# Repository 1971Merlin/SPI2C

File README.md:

# SPI2C
SPI2C interface hardware and software for the TEC-1 and SC-1 family of Z80 single board computers.

The full [construction article](SPI%20and%20I2C%20Article%20Final.pdf) PDF describes the SPI2C board in detail.

Please see https://github.com/tec1group for information on the TEC computer.

**spi2c_library.asm** contains the current code libraries for interfacing with the SPI2C board. Note the IO ports you choose to use will need to be edite in this file, if you're building for the TEC-1 hardware. The settings are correct for use with the SC-1 as provided.

PS2 Keyboard or Mouse contains sample code and circuit for hooking up a regular IBM PC compatible PS/2 or AT keyboard, or, a PS/2 mouse to the SPI2C.

-------------------------------------------------

The following code examples are early test releases and not all of them use the above library.

**spi_7segs.asm** links an 8 digit, 7-segment display (SPI bus, Duinotech XC-3714) to the SC1. 

**i2c test.asm** code expands on the first sample, adding a DS1307 based clock module (i2c bus, Duinotech XC-4450) which then displays the time on the 7-segment SPI board. The i2c code is also designed to be 'universal', compiling for either the TEC-1 or the SC-1 hardware platforms.

**i2c bus scan.asm** scans the entire i2c bus and displays the address of any detected i2c device on the 7-seg displays. press any key to display the next device. FFh displayed means 'no devices found'.

**5110.asm** displays an image on an SPI bus based 'Nokia 5510' or PCD8544 display, i.e. a standard 84x48 monochrome LCD.

**Game of Life 5110.asm** Game of Life is a cellular automation program developed in 1970. https://en.wikipedia.org/wiki/Conway%27s_Game_of_Life It is a popular routine to reproduce an many computing platforms, as the algorithm is quite simple and memory etc. requirements are also fairly minimal. In this version we use the SPI2C board and the Nokia 5110 LCD display as the output device. The program can be compiled with either a random or a fixed pattern starting point.

**maze 5100.asm** A simple maze program, made famous by the well known Commodore 64 basic code

````10 PRINT CHR$(205.5+RND(1)); : GOTO 10.````

Outputs to the 84x48 "Nokia 5110" LCD display.

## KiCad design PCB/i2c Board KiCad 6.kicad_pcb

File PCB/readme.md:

KiCad PCB Files for this project

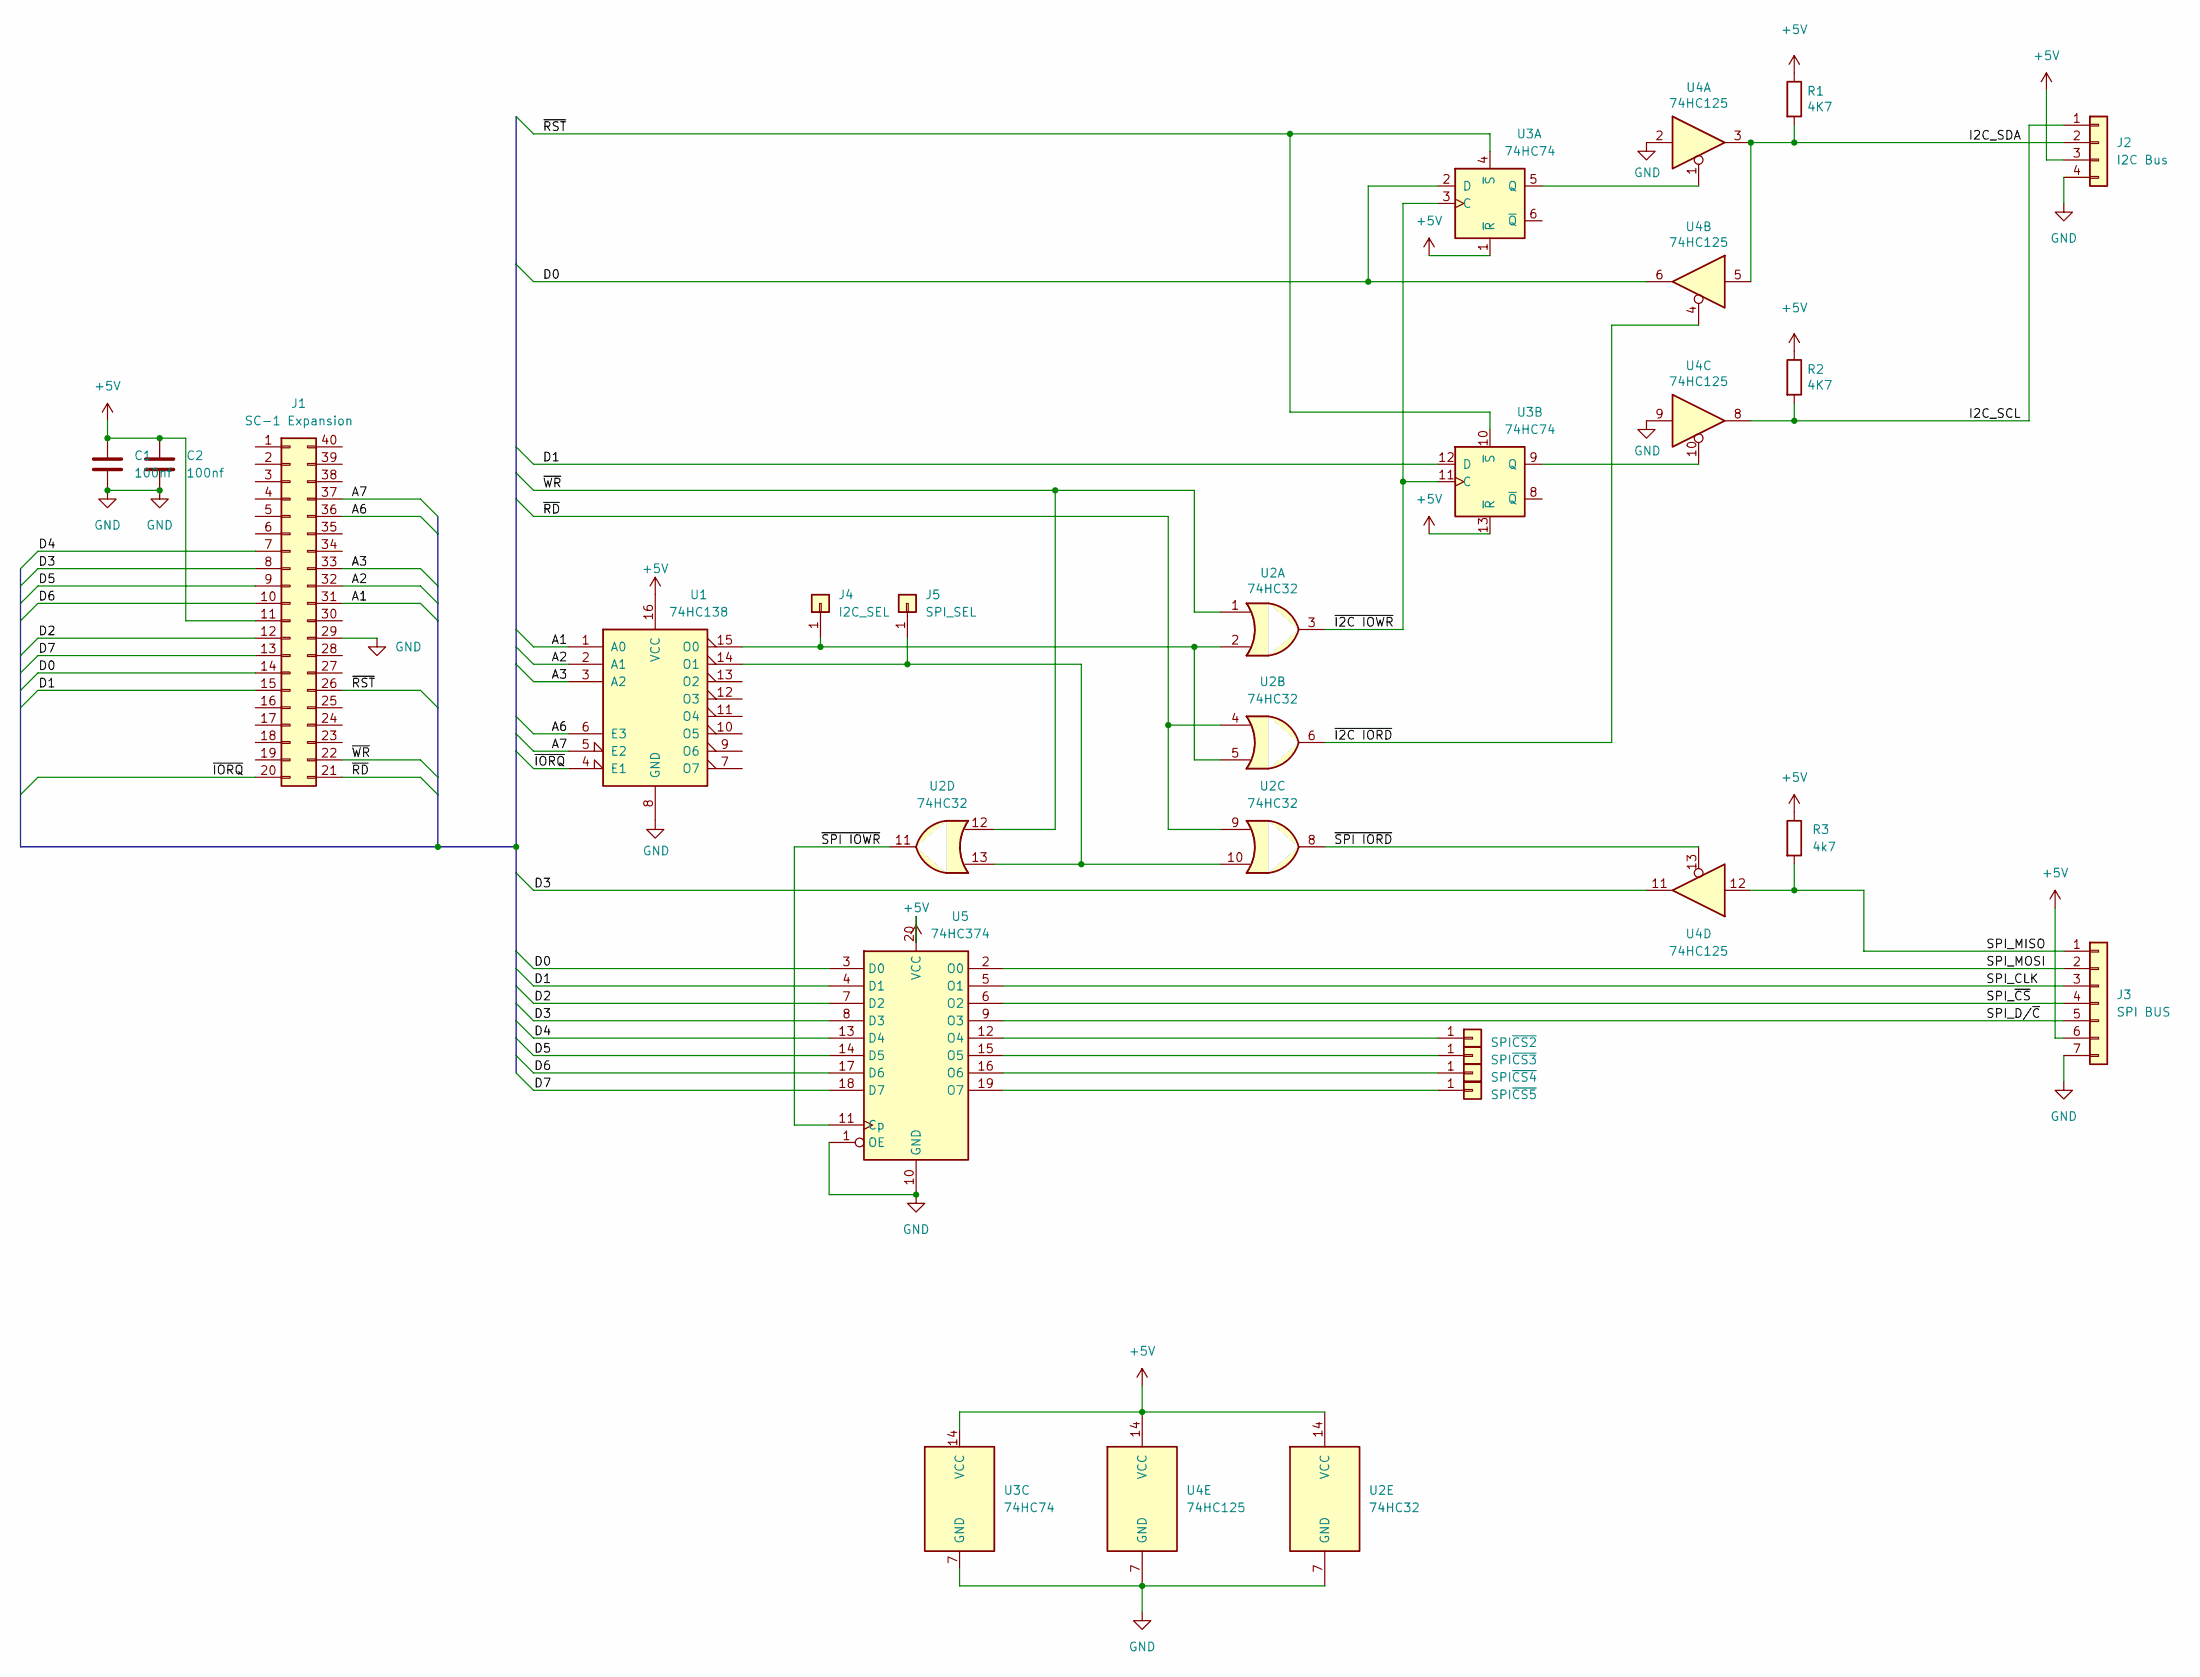
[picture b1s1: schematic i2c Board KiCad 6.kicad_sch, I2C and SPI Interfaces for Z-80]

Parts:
C1, C2: 100nf; C_Rect_L7.0mm_W2.0mm_P5.00mm
J1: SC-1 Expansion; SC-1 CPU IDC Header
J2: I2C Bus; PinSocket_1x04_P2.54mm_Vertical
J3: SPI BUS; PinSocket_1x07_P2.54mm_Vertical
J4: I2C_SEL; Pin_D1.0mm_L10.0mm
J5: SPI_SEL; Pin_D1.0mm_L10.0mm
J6: SPI~{CS2}; Pin_D1.0mm_L10.0mm
J7: SPI~{CS3}; Pin_D1.0mm_L10.0mm
J8: SPI~{CS4}; Pin_D1.0mm_L10.0mm
J9: SPI~{CS5}; Pin_D1.0mm_L10.0mm
R1, R2: 4K7; R_Axial_DIN0204_L3.6mm_D1.6mm_P5.08mm_Horizontal
R3: 4k7; R_Axial_DIN0204_L3.6mm_D1.6mm_P5.08mm_Horizontal
U1: 74HC138; DIP-16_W7.62mm_Socket
U2: 74HC32; DIP-14_W7.62mm_Socket
U3: 74HC74; DIP-14_W7.62mm_Socket
U4: 74HC125; DIP-14_W7.62mm_Socket
U5: 74HC374; DIP-20_W7.62mm_Socket

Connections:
+5V: C1.1, C2.1, J1.11, J2.3, J3.6, R1.1, R2.1, R3.1, U1.16 (VCC), U2.14 (VCC), U3.1 (~R), U3.13 (~R), U3.14 (VCC), U4.14 (VCC), U5.20 (VCC)
/A1: J1.31, U1.1 (A0)
/A2: J1.32, U1.2 (A1)
/A3: J1.33, U1.3 (A2)
/A6: J1.36, U1.6 (E3)
/A7: J1.37, U1.5 (E2)
/D0: J1.14, U3.2 (D), U4.6, U5.3 (D0)
/D1: J1.15, U3.12 (D), U5.4 (D1)
/D2: J1.12, U5.7 (D2)
/D3: J1.8, U4.11, U5.8 (D3)
/D4: J1.7, U5.13 (D4)
/D5: J1.9, U5.14 (D5)
/D6: J1.10, U5.17 (D6)
/D7: J1.13, U5.18 (D7)
/I2C_SCL: J2.1, R2.2, U4.8
/I2C_SDA: J2.2, R1.2, U4.3, U4.5
/SPI_CLK: J3.3, U5.5 (O1)
/SPI_D/~C: J3.5, U5.9 (O3)
/SPI_MISO: J3.1, R3.2, U4.12
/SPI_MOSI: J3.2, U5.2 (O0)
/SPI_~CS: J3.4, U5.6 (O2)
/~I2C IORD: U2.6, U4.4
/~I2C IOWR: U2.3, U3.3 (C), U3.11 (C)
/~IORQ: J1.20, U1.4 (E1)
/~RD: J1.21, U2.4, U2.9
/~RST: J1.26, U3.4 (~S), U3.10 (~S)
/~SPI IORD: U2.8, U4.13
/~SPI IOWR: U2.11, U5.11 (Cp)
/~WR: J1.22, U2.1, U2.12
GND: C1.2, C2.2, J1.29, J2.4, J3.7, U1.8 (GND), U2.7 (GND), U3.7 (GND), U4.2, U4.7 (GND), U4.9, U5.1 (OE), U5.10 (GND)
unnamed: J4.1, U1.15 (O0), U2.2, U2.5
unnamed: J5.1, U1.14 (O1), U2.10, U2.13
unnamed: J6.1, U5.12 (O4)
unnamed: J7.1, U5.15 (O5)
unnamed: J8.1, U5.16 (O6)
unnamed: J9.1, U5.19 (O7)
unnamed: U3.5 (Q), U4.1
unnamed: U3.9 (Q), U4.10

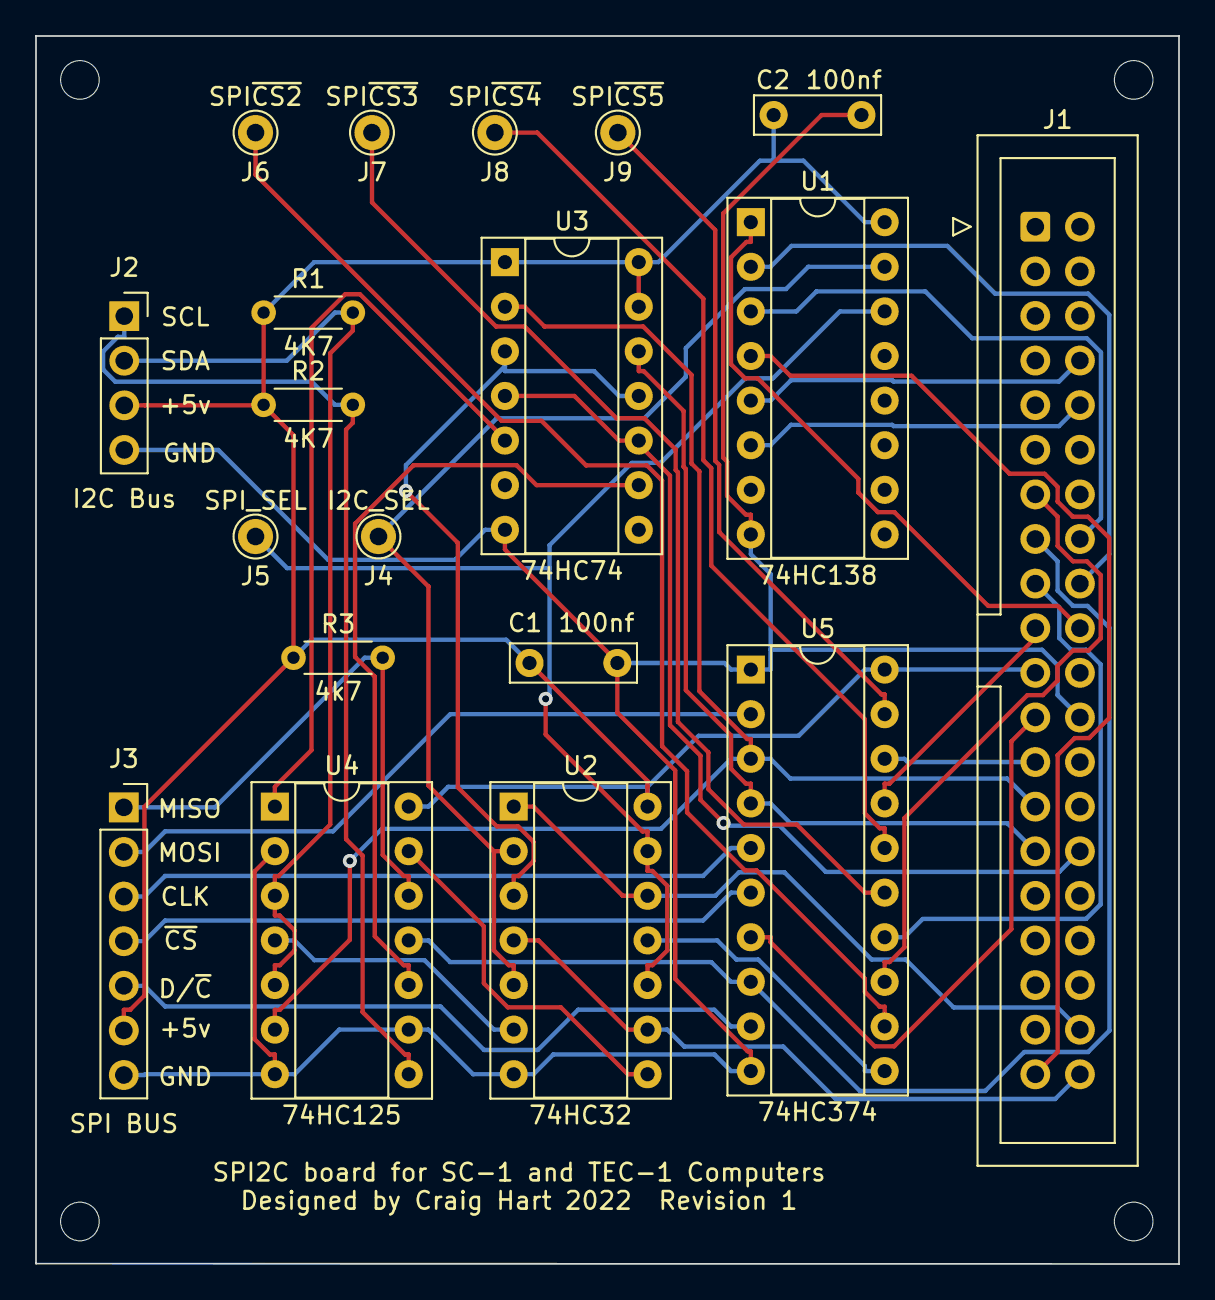
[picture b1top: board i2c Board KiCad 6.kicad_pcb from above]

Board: 2 copper layers, 65.1 x 69.9 mm, 23 parts (0 on the bottom side), 38 nets.

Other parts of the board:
Hole1, Hole2, Hole3, Hole4: MountingHole_2.2mm_M2

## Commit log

2022-01-28 Initial Files
2022-01-28 Intial Article content
2022-01-28 Removed unnecessary delay loop
2022-01-28 Datasheet for Tiny RTC module - Duniotech XC-4450
2022-01-31 Updated Schematic
    Added propper connectors, additional SPI bus pin supproting D/C signal used by many SPI devices.
2022-02-05 Updated Comments; no code changes
2022-02-05 Sample code for fully populated SPI2C board
    Sample code for the SPI2C board. Supports the following devices:
    SPI: MAX7219 8-digit, 7-segment display; Duinotech XC-3714 or equivilant
    I2C: DS1307 RTC board; Duinotech XC-4450 or equivilant
    Currnently only runs on the SC-1 but is being programmed to support both TEC-1 and SC-1 via a conditional compile statement.
2022-02-05 TEC-1 compile target
    Revised code to conditional compile for TEC-1; supports 7-seg display differences
2022-02-06 Code Cleanup, add date function
    Press any keyboard key to toggle between time and date.
    Date format is YY-MM-DD
2022-02-09 SetDS1307 chip, cleanups
    Programs the DS1307 chip with some useable values; clock starts at 18:30:00 and date is 07/10/22
    Cleanups of i2c code and removes some unnecessary subroutines
2022-02-12 Polled keyboard, more SPI fixes
    Pressing a keyboard key no longer freezes the code
    SPI code optimized for DS1037
2022-02-13 Article on developing for the TEC on a PC
2022-02-13 Code to support an 84x48 SPI bus based LCD display
    SPI2C board code for the "Nokia 5110" or Philips PCD8544 family of dispalys. e.g. Duinotech XC-4616
2022-02-13 Datashhet for the 84x48 display
2022-02-20 Finds I2C devices by their bus address
    Scans the I2C bus and displays any valid devices by their address on the 7-Seg displays.
    Checks all valid address 00h - 7fh
    Press any key to show the next detected address. Display of FF means no devices detected.
    DS1307 RTC should appear at 68h
    24LC16B, 24C32 etc. Serial SRAMs appear at 50..57h depending on model and wiring.
    Note the Duinotech XC-4450 contains a 24C32N at address 50h as well as the DS1307 at 68h
2022-03-06 John Conway's game of Life for SPI2C and 84x48 LCD
2022-04-07 Simple 'maze' for the Nokia 5110 84x48 LCD
    Based on the classic 10 PRINT CHR$(205.5+RND(1)); : GOTO 10 code made famous by the Commodore 64
2022-09-22 PCB and Circuit high resolution images
2022-09-22 Final Kicad PCB files complete
2023-07-04 Universal code Library for SPI2C board
2023-07-04 Add shift-keys support
    Added shift support for non-alpha keys, support numeric / and Enter keys.
